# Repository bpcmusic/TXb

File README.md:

# TXb - 2HP i2c Bus Board w/ 3.5mm Connectors

The TELEXb (TXb) is a 2HP powered bus board for the i2c ecosystem that also enables the connection of external devices using the two 3.5mm stereo jacks at the top and the bottom of the module. These jacks can be used for connection to the 16n FaderBank, TXb that are in disconnected rack rows, or to fiendishly wonderful Frankenstein machines of your own creation.

## High-Level i2c Tips

There are some key things to keep in mind with the TXb (and i2c busses in general):

- Powered bus boards are required when you connect three or more devices to your Teletype via i2c.
- You should only have one bus board connected to power at a time.
- Connections should be kept as short as possible using high-quality cabling (less than 3.5mm).
- There still are practical limits to having a stable i2c bus that are highly dependent on the topology of your deployment. Plan for some trial and error.

Want more help understanding what i2c can and can't do and how to use it in your setup? Check out this awesome [User's Guide to i2c](https://llllllll.co/t/a-users-guide-to-i2c/19219) that was put together by some awesome people.

## Module Specifications

- +12V: 1 mA 
- -12V: 0 mA
- +5V: 0 mA
- 2HP
- 20.5mm Depth

## Folders & Files Explained

* **assistive**: 
	* ```TXb Frame``` - a 3D printed frame to hold multiple TXb at a time
	* ```TXb Stencil Frame``` - a 3D printed stencil frame to hold the TXb in place while applying solder paste
	* ```TXb Stencil.svg``` - the solder paste stencil for laser cutting
	
* **board**
	* ```gerbers``` - the gerbers files (and Eagle files) for the PCB
	* ```images``` - image rederings of the PCB
	* ```TELEXb_v1.2.brd/sch``` - the master Eagle file for the TXb
	
* **extras**
	* ```instructions.docx``` - the instructions delivered with the pre-built module
	
* **panel**
	* ```metalphoto``` - the individual files used for the creation of the metalphoto panel in the retail version
	* ```TXb.ai/svg``` - the panel files
	* ```TXb_lasercut.svg``` - the file used for cutting prototype panels out of acrylic
	* ```TXb_lg.png``` - a big version of the panel
	* ```TXb_mp.zip``` - the archive sent for fabrication
	* ```TXb_sm.png``` - a small photo of the panel

* ```TXb BOM.csv``` - the BOM for this version of the TXb.

## Links

Visit the TXb on Modular Grid:

* [Modular Grid](https://www.modulargrid.net/e/other-unknown-telexb)

Pre-built TXb are occasionally made availalbe for purchase here:

* [store.bpcmusic.com](https://store.bpcmusic.com/products/telexb)

## License

[CC BY-SA 4.0](http://creativecommons.org/licenses/by-sa/4.0/)

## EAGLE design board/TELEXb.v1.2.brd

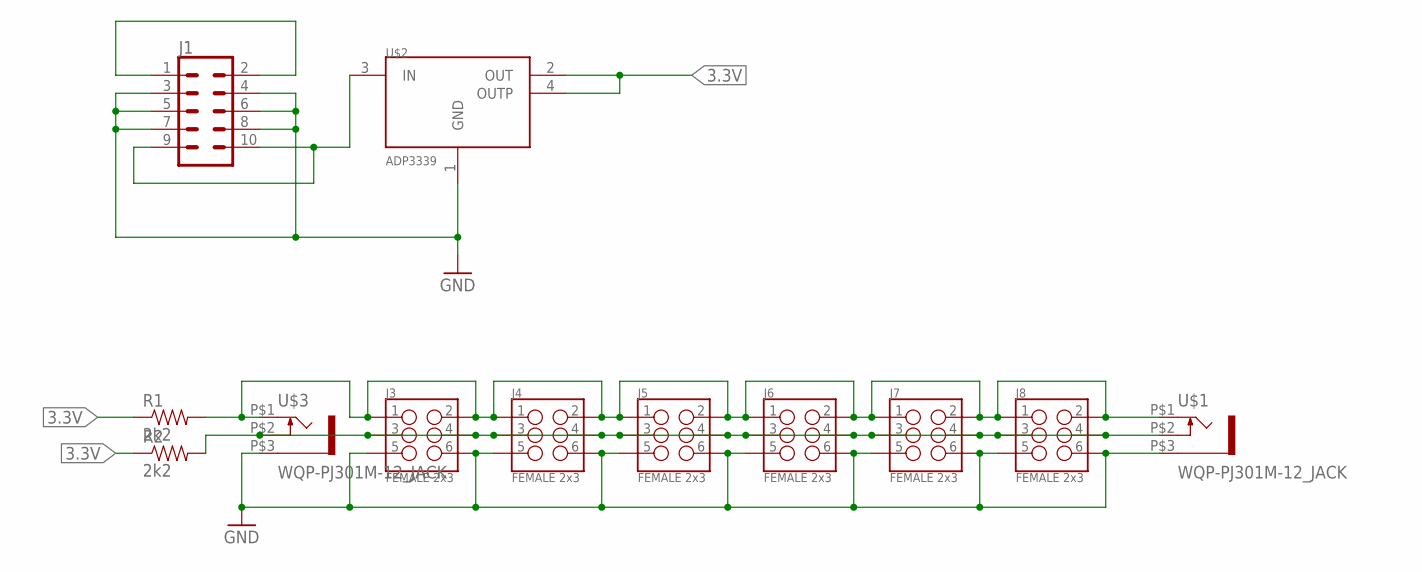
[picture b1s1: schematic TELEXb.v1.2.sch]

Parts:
J1: CONN_05X2SHD; 2X5-SHROUDED
J3, J4, J5, J6, J7, J8: FEMALE 2x3; 2X3
R1, R2: 2k2; 1206
U$1, U$3: WQP-PJ301M-12_JACK
U$2: ADP3339; SOT223

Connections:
3.3V: R1.1, R2.1, U$2.2 (OUT), U$2.4 (OUTP)
GND: J1.3, J1.4, J1.5, J1.6, J1.7, J1.8, J3.5, J3.6, J4.5, J4.6, J5.5, J5.6, J6.5, J6.6, J7.5, J7.6, J8.5, J8.6, U$1.P$3 (1), U$2.1 (GND), U$3.P$3 (1)
unnamed: J1.9, J1.10, U$2.3 (IN)
unnamed: J3.1, J3.2, J4.1, J4.2, J5.1, J5.2, J6.1, J6.2, J7.1, J7.2, J8.1, J8.2, R1.2, U$1.P$1 (2), U$3.P$1 (2)
unnamed: J1.1, J1.2
unnamed: J3.3, J3.4, J4.3, J4.4, J5.3, J5.4, J6.3, J6.4, J7.3, J7.4, J8.3, J8.4, R2.2, U$1.P$2 (3), U$3.P$2 (3)

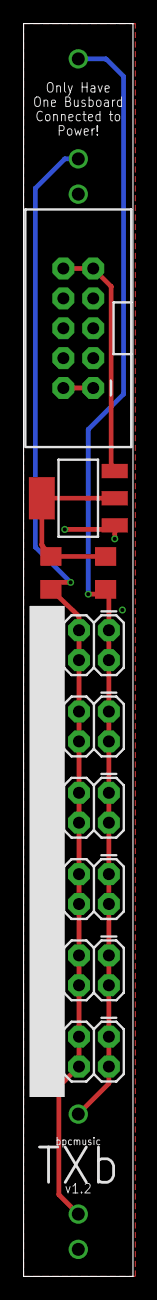
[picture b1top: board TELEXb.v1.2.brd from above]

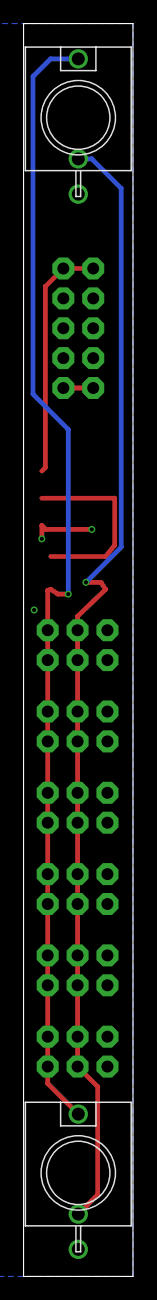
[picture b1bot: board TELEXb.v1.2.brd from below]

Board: 2 copper layers, 9.3 x 106.5 mm, 12 parts (2 on the bottom side), 6 nets.

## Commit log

2019-02-14 added a pic

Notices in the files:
parts and their libraries:
SparkFun-Connectors: Licensing: Creative Commons ShareAlike 4.0 International - https://creativecommons.org/licenses/by-sa/4.0
